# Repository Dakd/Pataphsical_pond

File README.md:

# Pataphsical_pond  
정리안됨 주의!
제작과정 및 작품영상 http://coso.tistory.com/category/Artwork/Pataphsical%20pond

-추가테스트-

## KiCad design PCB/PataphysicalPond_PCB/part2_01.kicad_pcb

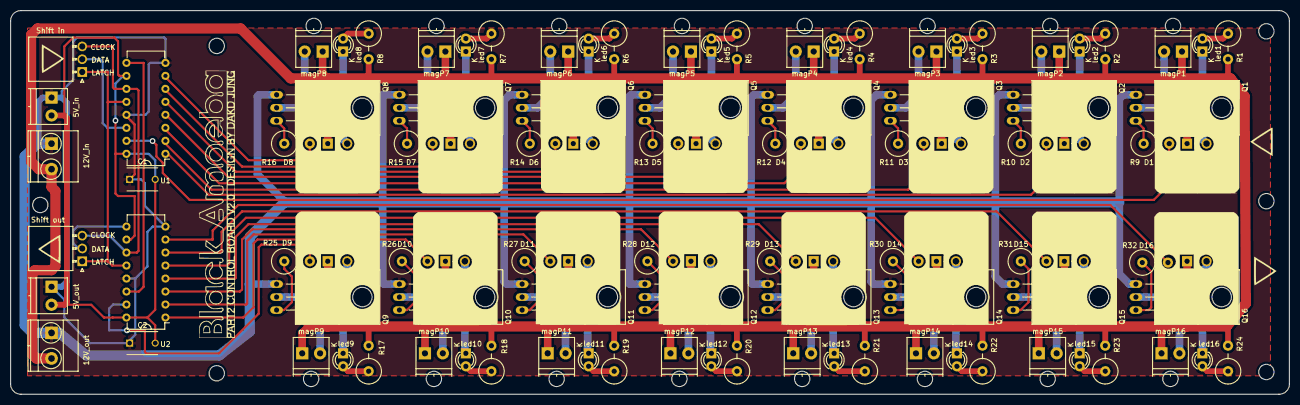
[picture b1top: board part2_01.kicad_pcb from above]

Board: 2 copper layers, 250.0 x 75.0 mm, 106 parts (0 on the bottom side), 72 nets.

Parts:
5V_in: 5V_IN; TerminalBlock_Pheonix_PT-3.5mm_2pol
5V_out: 5V_OUT; TerminalBlock_Pheonix_PT-3.5mm_2pol
12V_in: 12V_IN; TerminalBlock_Pheonix_MKDS1.5-2pol
12V_out: 12V_OUT; TerminalBlock_Pheonix_MKDS1.5-2pol
C1, C2: 0.1uF; C_Disc_D6_P5
D1, D2, D3, D4, D5, D6, D7, D8, D9, D10, D11, D12, D13, D14, D15, D16: 1N4001; Diode_DO-41_SOD81_Vertical_AnodeUp
Q1, Q2, Q3, Q4, Q5, Q6, Q7, Q8, Q9, Q10, Q11, Q12, Q13, Q14, Q15, Q16: 50N06; TO-220_Neutral123_Horizontal_Reverse
R1, R2, R3, R4, R5, R6, R7, R8, R9, R10, R11, R12, R13, R14, R15, R16, R17, R18, R19, R20, R21, R22, R23, R24, R25, R26, R27, R28, R29, R30, R31, R32: 10kΩ; Resistor_Vertical_RM5mm
Shift in: Shift in; Molex_NanoFit_1x03x2.50mm_Angled
Shift out: Shift out; Molex_NanoFit_1x03x2.50mm_Angled
U1, U2: 74HC595; DIP-16_W7.62mm
led1, led2, led3, led4, led5, led6, led7, led8, led9, led10, led11, led12, led13, led14, led15, led16: LED; LED-3MM
magP1, magP2, magP3, magP4, magP5, magP6, magP7, magP8, magP9, magP10, magP11, magP12, magP13, magP14, magP15, magP16: MAG; TerminalBlock_Pheonix_PT-3.5mm_2pol

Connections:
+5V: 5V_in.2, 5V_out.2, C1.2, C2.2, U1.10, U1.16, U2.10, U2.16
+12V: 12V_in.2, 12V_out.2, D1.1, D2.1, D3.1, D4.1, D5.1, D6.1, D7.1, D8.1, D9.1, D10.1, D11.1, D12.1, D13.1, D14.1, D15.1, D16.1, R1.2, R2.2, R3.2, R4.2, R5.2, R6.2, R7.2, R8.2, R17.2, R18.2, R19.2, R20.2, R21.2, R22.2, R23.2, R24.2, magP1.1, magP2.1, magP3.1, magP4.1, magP5.1, magP6.1, magP7.1, magP8.1, magP9.1, magP10.1, magP11.1, magP12.1, magP13.1, magP14.1, magP15.1, magP16.1
GND: 5V_in.1, 5V_out.1, 12V_in.1, 12V_out.1, C1.1, C2.1, Q1.3, Q2.3, Q3.3, Q4.3, Q5.3, Q6.3, Q7.3, Q8.3, Q9.3, Q10.3, Q11.3, Q12.3, Q13.3, Q14.3, Q15.3, Q16.3, U1.8, U1.13, U2.8, U2.13
unnamed: D1.2, Q1.2, led1.1, magP1.2
unnamed: D2.2, Q2.2, led2.1, magP2.2
unnamed: D3.2, Q3.2, led3.1, magP3.2
unnamed: D4.2, Q4.2, led4.1, magP4.2
unnamed: D5.2, Q5.2, led5.1, magP5.2
unnamed: D6.2, Q6.2, led6.1, magP6.2
unnamed: D7.2, Q7.2, led7.1, magP7.2
unnamed: D8.2, Q8.2, led8.1, magP8.2
unnamed: D9.2, Q9.2, led9.1, magP9.2
unnamed: D10.2, Q10.2, led10.1, magP10.2
unnamed: D11.2, Q11.2, led11.1, magP11.2
unnamed: D12.2, Q12.2, led12.1, magP12.2
unnamed: D13.2, Q13.2, led13.1, magP13.2
unnamed: D14.2, Q14.2, led14.1, magP14.2
unnamed: D15.2, Q15.2, led15.1, magP15.2
unnamed: D16.2, Q16.2, led16.1, magP16.2
unnamed: Shift in.1, Shift out.1, U1.12, U2.12
unnamed: Shift in.2, U1.14
unnamed: Shift in.3, Shift out.3, U1.11, U2.11
unnamed: Shift out.2, U2.9
unnamed: Q1.1, R9.1
unnamed: Q2.1, R10.1
unnamed: Q3.1, R11.1
unnamed: Q4.1, R12.1
unnamed: Q5.1, R13.1
unnamed: Q6.1, R14.1
unnamed: Q7.1, R15.1
unnamed: Q8.1, R16.1
unnamed: Q9.1, R25.1
unnamed: Q10.1, R26.1
unnamed: Q11.1, R27.1
unnamed: Q12.1, R28.1
unnamed: Q13.1, R29.1
unnamed: Q14.1, R30.1
unnamed: Q15.1, R31.1
unnamed: Q16.1, R32.1
unnamed: R1.1, led1.2
unnamed: R2.1, led2.2
unnamed: R3.1, led3.2
unnamed: R4.1, led4.2
unnamed: R5.1, led5.2
unnamed: R6.1, led6.2
unnamed: R7.1, led7.2
unnamed: R8.1, led8.2
unnamed: R9.2, U1.15
unnamed: R10.2, U1.1
unnamed: R11.2, U1.2
unnamed: R12.2, U1.3
unnamed: R13.2, U1.4
unnamed: R14.2, U1.5
unnamed: R15.2, U1.6
unnamed: R16.2, U1.7
unnamed: R17.1, led9.2
unnamed: R18.1, led10.2
unnamed: R19.1, led11.2
unnamed: R20.1, led12.2
unnamed: R21.1, led13.2
unnamed: R22.1, led14.2
unnamed: R23.1, led15.2
unnamed: R24.1, led16.2
unnamed: R25.2, U2.15
unnamed: R26.2, U2.1
unnamed: R27.2, U2.2
unnamed: R28.2, U2.3
unnamed: R29.2, U2.4
unnamed: R30.2, U2.5
unnamed: R31.2, U2.6
unnamed: R32.2, U2.7
unnamed: U1.9, U2.14

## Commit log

2018-02-24 original
2018-04-02 추가수정 테스트1
    추가수정 테스트1 내용
